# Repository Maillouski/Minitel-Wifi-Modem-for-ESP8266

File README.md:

# Minitel WiFi Modem for North American version of Alcatel Minitel 1B.

The pinout od the DIN socket of the US/CAN version of the Telic-Acatel Minitel 1B is different.

PIN 1 : RS232C RX

PIN 2 : Uknown

PIN 3 GND

PIN 4 Unknown

PIN 5 RS232C TX

PIN 6 RS232C DTR

 Serial WiFi Modem for Minitel Using ESP8266
 
 Largely based on Richard Bettridge's Vintage Computer WiFi Modem
 
 See https://github.com/ssshake/vintage-computer-wifi-modem

 MAX3232 Adapter board based on Richard Bettridge desing.

 Thanks to Éric Sérandour for the Minitel1B_Hard library (https://github.com/eserandour/Minitel1B_Hard)
 
 Thank to Louis H. (https://github.com/iodeo) and Hervé Warin (https://github.com/64rulez) for their help!

 I added Websocket dialing support for Minitel services along with
 some Minitel related features.

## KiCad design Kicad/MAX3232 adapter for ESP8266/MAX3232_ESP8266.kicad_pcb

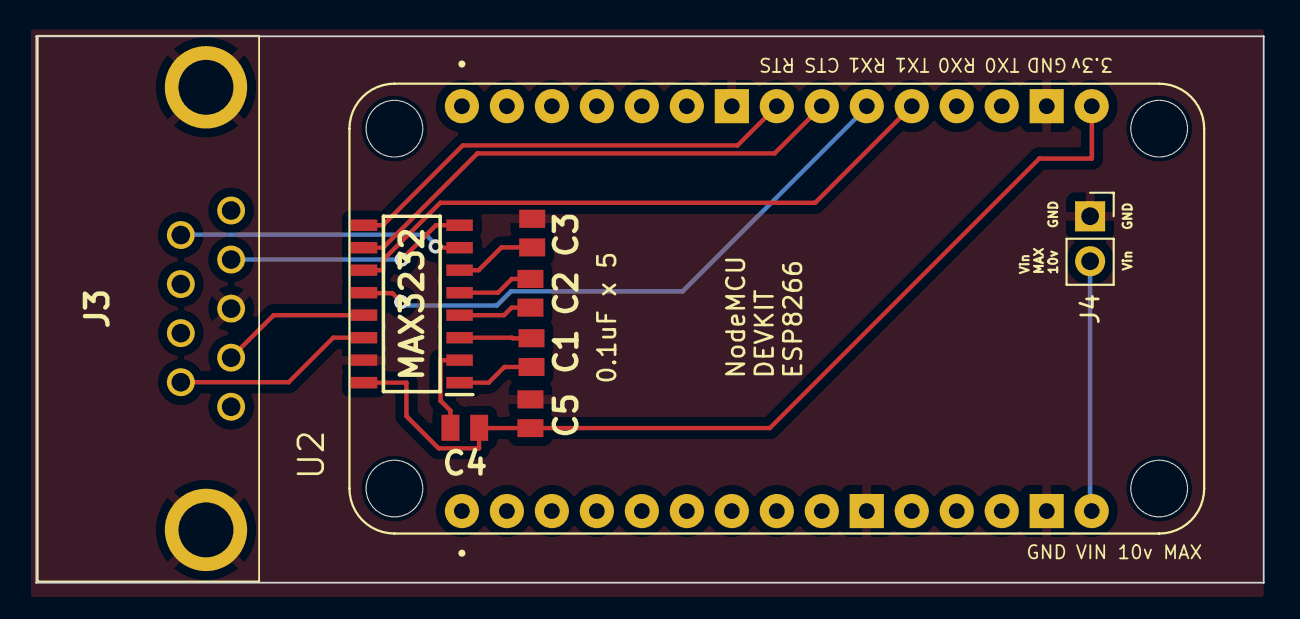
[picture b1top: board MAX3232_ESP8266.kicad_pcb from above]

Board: 2 copper layers, 69.3 x 30.9 mm, 9 parts (0 on the bottom side), 17 nets.

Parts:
C1, C2, C3, C4, C5: C; CAPC2012X94N
J3: DE9_Receptacle_MountingHoles; L77SDE09SA4CH4F
J4: Conn_01x02_Pin; PinSocket_1x02_P2.54mm_Vertical
MAX3232: SP3232EEN-L_TR; SOIC127P600X175-16N
U2: NodeMCU_1.0_(ESP-12E); NodeMCU_ESP8266_SEEED_113990105

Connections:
+3.3V: C4.1, C5.2, MAX3232.16 (VCC), U2.16 (3.3V)
GND2: C3.2, C5.1, J3.5, J3.MH1 (PAD), J3.MH2 (PAD), J4.2, MAX3232.15 (GND), U2.10 (GND), U2.14 (GND), U2.17 (GND), U2.24 (GND)
unnamed: C1.1, MAX3232.1 (C1+)
unnamed: C1.2, MAX3232.3 (C1-)
unnamed: C2.1, MAX3232.4 (C2+)
unnamed: C2.2, MAX3232.5 (C2-)
unnamed: J3.3, MAX3232.13 (R1IN)
unnamed: MAX3232.12 (R1OUT), U2.21 (D7(GPIO13))
unnamed: J3.7, MAX3232.8 (R2IN)
unnamed: MAX3232.9 (R2OUT), U2.23 (D5(GPIO14))
unnamed: MAX3232.11 (T1IN), U2.20 (D8(GPIO15))
unnamed: J3.2, MAX3232.14 (T1OUT)
unnamed: MAX3232.10 (T2IN), U2.22 (D6(GPIO12))
unnamed: J3.8, MAX3232.7 (T2OUT)
unnamed: C4.2, MAX3232.2 (V+)
unnamed: C3.1, MAX3232.6 (V-)
unnamed: J4.1, U2.15 (VIN)

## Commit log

2024-05-05 Moved files arounf for Arduino IDE
2024-05-06 Speed Dials update and screen Mode handling
